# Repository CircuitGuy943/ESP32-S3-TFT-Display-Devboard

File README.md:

# ESP32 TFT Display Devboard

The ESP TFT Devboard is a devboard based on the ESP32-S3-WROOM-1 module with an integrated 40-pin connector designed to fully operate a TFT Display (one with a 3x8 RGB parallel interface) from the USB C connector only for power. It also has a bunch of breakout headers so that the GPIO pins can be accessed and used for other things, like a normal devboard whenever the display isn't being used. It consists of two USB C ports, one using the ESP32's built in USB connection and another using a USB to UART bridge (There is also a diode on each to ensure that the 5V doesn't backfeed if both USBs are connected). It then also consists of a boost converter to 24V for the LED Backlight and a current sink regulator to ensure it doesn't consume more than the rated current of 70mA.

## Features:
- Everything found on a normal devboard
- 2x USB C ports
- 24V, 5V and 3.3V outputs
- Support for a TFT 3x8 RGB display

## PCB
And this is my PCB. Very difficult to include everything in two layers but I managed to do it to save cost, and ommitted the use of an via in pads, the USB traces are length matched but the signals for the display don't need any trace/impedance matching as they don't run fast enough.

And the Schematic:

And here are some 3D views as well:

## Firmware Overview
I've included some basic firmware (**untested**) to get the TFT working but other than that it should function like a normal devboard hosting an ESP32

## BOM:
I have also included a .csv with the BOM list but here it is anyways.

 - 1x	CH340C	
 - 3x	Diode	
 - 2x	2N3904	
 - 2x	USB_C_Receptacle_USB2.0_16P	
 - 2x	5.7K	
 - 4x	5.1K	
 - 1x	47K	
 - 4x	1K	
 - 1x	1uF	
 - 3x	0.1uF
 - 4x	10uF
 - 6x	10K
 - 4x	27R
 - 1x	396K
 - 2x	100R
 - 1x	10K
 - 1x	MT3608
 - 1x	LD1117S33TR_SOT223
 - 1x	22R
 - 1x	ESP32-S3-WROOM-1
 - 2x	22uF
 - 1x	22uH
 - 2x	RED Led
 - 1x	GREEN Led
 - 2x	SW_Push
 - 1x	Conn_01x40_Socket
 - 1x	CAT4104
 - 1x	1.8K
 - 2x	Conn_01x14_Pin
 - 2x	Conn_01x04_Pin
 - 2x	Conn_01x09_Pin
(All parts for one devboard only)

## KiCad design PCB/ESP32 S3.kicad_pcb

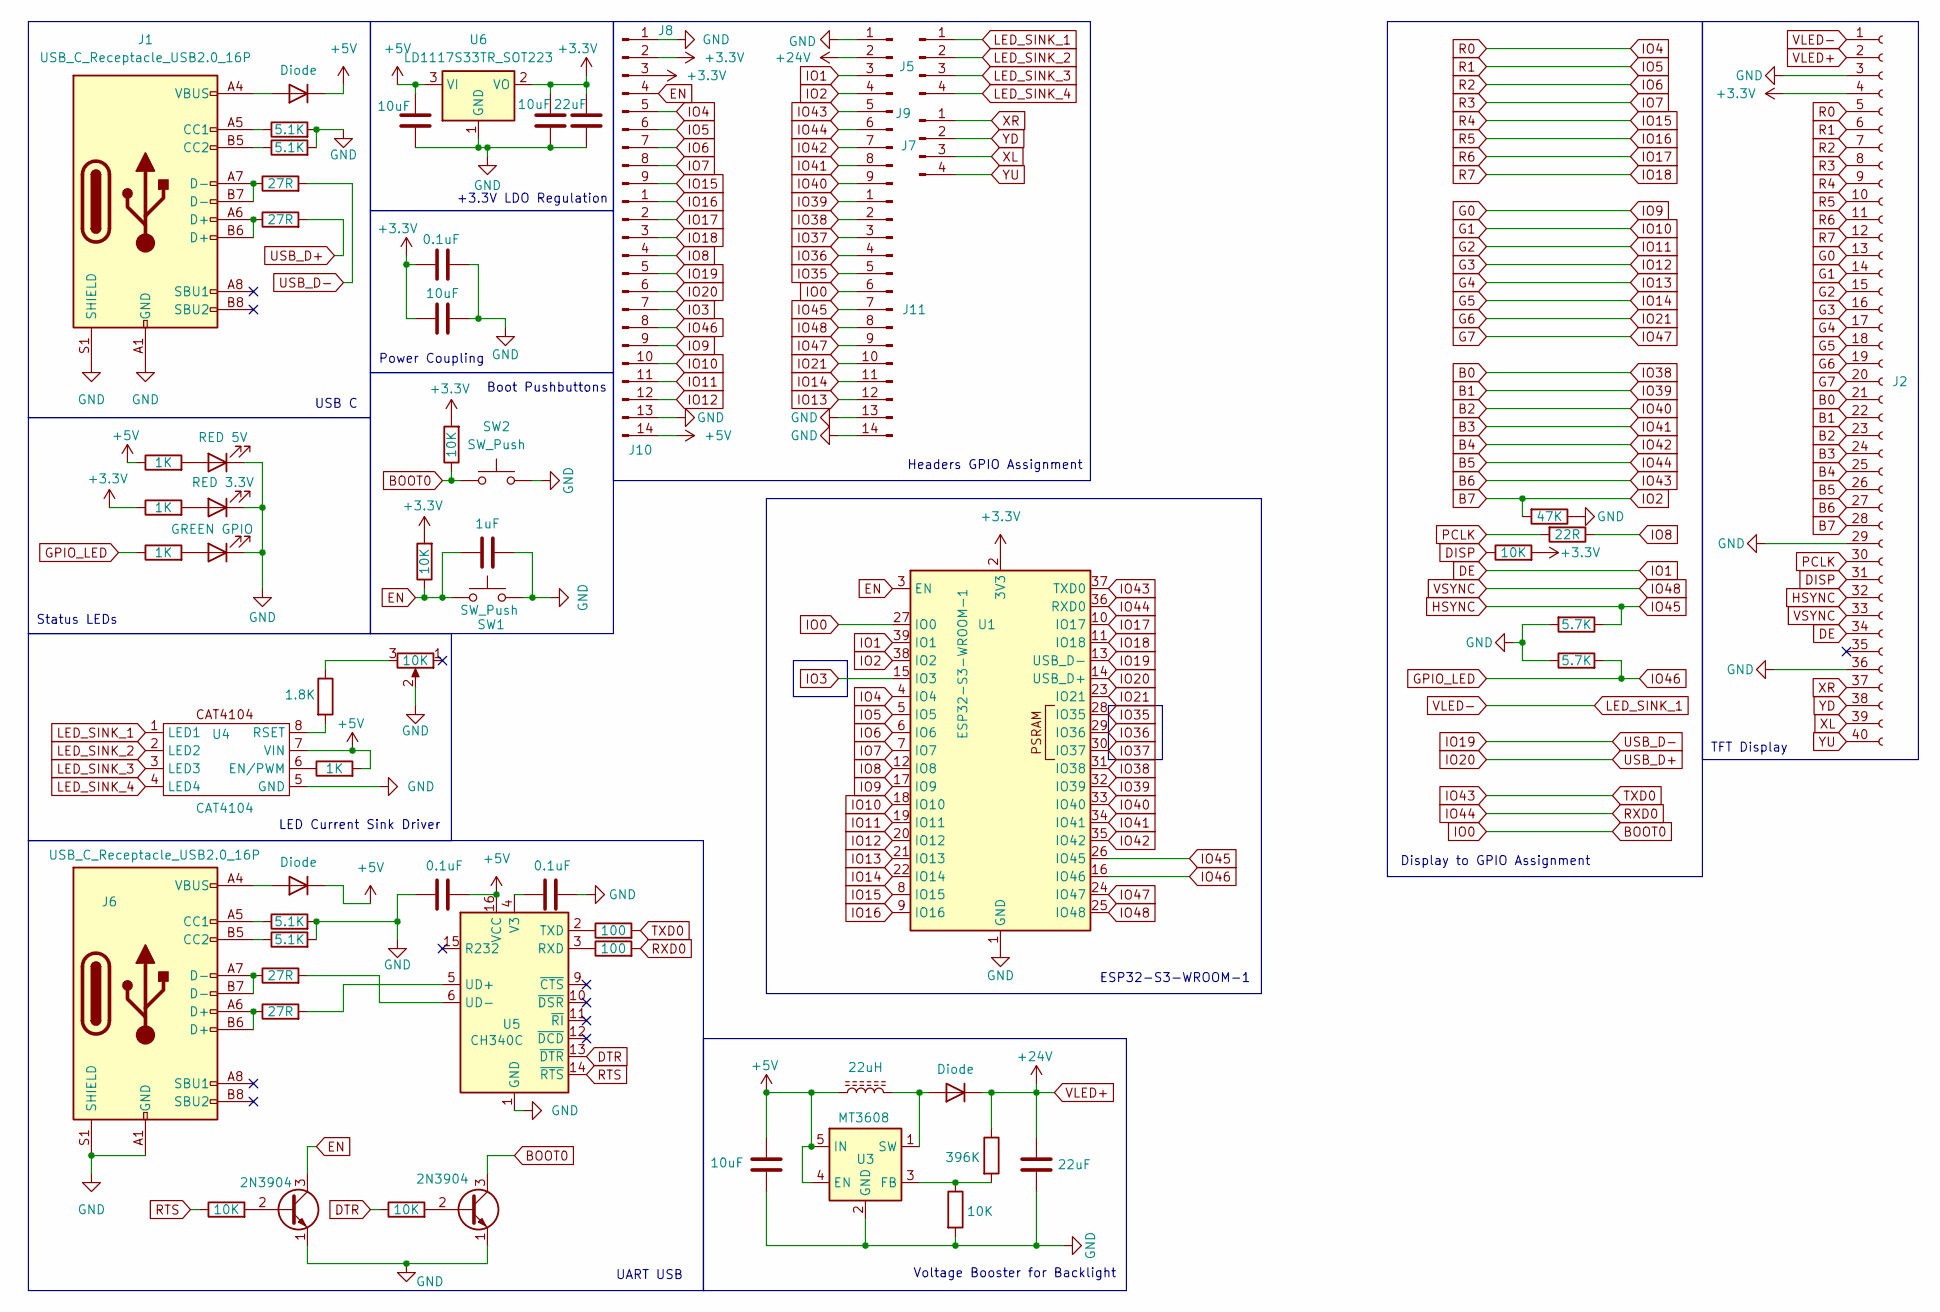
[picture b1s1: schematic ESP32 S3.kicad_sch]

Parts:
C1, C7, C8: 0.1uF; C_0402_1005Metric
C2, C3, C4, C6: 10uF; C_0603_1608Metric
C5, C9: 22uF; C_0603_1608Metric
C10: 1uF; C_0402_1005Metric
D1: RED 5V; LED_0402_1005Metric
D2: RED 3.3V; LED_0402_1005Metric
D3: GREEN GPIO; LED_0402_1005Metric
D4, D5, D6: Diode; D_SMB
J1, J6: USB_C_Receptacle_USB2.0_16P; USB_C_Receptacle_HCTL_HC-TYPE-C-16P-01A
J2: Conn_01x40_Socket; Hirose_FH12-40S-0.5SH_1x40-1MP_P0.50mm_Horizontal
J5, J7: Conn_01x04_Pin; PinHeader_1x04_P2.54mm_Vertical
J8, J9: Conn_01x09_Pin; PinHeader_1x09_P2.54mm_Vertical
J10, J11: Conn_01x14_Pin; PinHeader_1x14_P2.54mm_Vertical
L1: 22uH; 5028_SMD_INDUCTOR_SRR5028-220Y
Q1, Q2: 2N3904; SOT-23
R1, R2, R21, R22: 5.1K; R_0402_1005Metric
R3, R4, R19, R20: 27R; R_0402_1005Metric
R5, R6, R12, R14: 1K; R_0402_1005Metric
R7, R17: 5.7K; R_0402_1005Metric
R8, R9, R11, R15, R25, R26: 10K; R_0402_1005Metric
R10: 396K; R_0402_1005Metric
R13: 1.8K; R_0402_1005Metric
R18: 22R; R_0402_1005Metric
R23, R24: 100; R_0402_1005Metric
R27: 47K; R_0402_1005Metric
RV1: 10K; Potentiometer_Bourns_3314J_Vertical
SW1, SW2: SW_Push; SW_Push_1P1T-SH_NO_CK_KMR2xxG
U1: ESP32-S3-WROOM-1
U3: MT3608; SOT-23-6
U4: CAT4104
U5: CH340C; SOIC-16_3.9x9.9mm_P1.27mm
U6: LD1117S33TR_SOT223; SOT-223-3_TabPin2

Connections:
+3.3V: C1.2, C2.2, C4.2, C9.2, J2.4, J8.2, J8.3, R6.1, R8.2, R9.2, R15.2, U1.2 (3V3), U6.2 (VO)
+5V: C3.1, C6.2, C8.2, D5.1 (K), D6.1 (K), J10.14, L1.1, R5.1, R12.2, U3.4 (EN), U3.5 (IN), U4.7 (VIN), U5.16 (VCC), U6.3 (VI)
B0: J2.21, J11.2, U1.31 (IO38)
B1: J2.22, J11.1, U1.32 (IO39)
B2: J2.23, J9.9, U1.33 (IO40)
B3: J2.24, J9.8, U1.34 (IO41)
B4: J2.25, J9.7, U1.35 (IO42)
B5: J2.26, J9.6, R23.2, U1.36 (RXD0)
B6: J2.27, J9.5, R24.2, U1.37 (TXD0)
B7: J2.28, J9.4, R27.2, U1.38 (IO2)
BOOT0: J11.6, Q2.3 (C), R9.1, SW2.1, U1.27 (IO0)
DE: J2.34, J9.3, U1.39 (IO1)
DISP: J2.31, R15.1
DTR: R25.1, U5.13 (~DTR)
EN: C10.2, J8.4, Q1.3 (C), R8.1, SW1.1, U1.3 (EN)
G0: J2.13, J10.9, U1.17 (IO9)
G1: J2.14, J10.10, U1.18 (IO10)
G2: J2.15, J10.11, U1.19 (IO11)
G3: J2.16, J10.12, U1.20 (IO12)
G4: J2.17, J11.12, U1.21 (IO13)
G5: J2.18, J11.11, U1.22 (IO14)
G6: J2.19, J11.10, U1.23 (IO21)
G7: J2.20, J11.9, U1.24 (IO47)
GND: C1.1, C2.1, C3.2, C4.1, C5.1, C6.1, C7.2, C8.1, C9.1, C10.1, D1.1 (K), D2.1 (K), D3.1 (K), J1.A1 (GND), J1.A12 (GND), J1.B1 (GND), J1.B12 (GND), J1.S1 (SHIELD), J2.3, J2.29, J2.36, J2.MP, J6.A1 (GND), J6.A12 (GND), J6.B1 (GND), J6.B12 (GND), J6.S1 (SHIELD), J8.1, J9.1, J10.13, J11.13, J11.14, Q1.1 (E), Q2.1 (E), R1.2, R2.2, R7.1, R11.2, R17.2, R21.2, R22.2, R27.1, RV1.2, SW1.2, SW1.SH, SW2.2, SW2.SH, U1.1 (GND), U1.40 (GND), U1.41 (GND), U3.2 (GND), U4.5 (GND), U5.1 (GND), U6.1 (GND)
GPIO19: J10.5, R3.2, U1.13 (USB_D-)
GPIO20: J10.6, R4.2, U1.14 (USB_D+)
GPIO_LED: J10.8, R7.2, R14.1, U1.16 (IO46)
HSYNC: J2.32, J11.7, R17.1, U1.26 (IO45)
IO3: J10.7, U1.15 (IO3)
IO4: J2.5, J8.5, U1.4 (IO4)
IO5: J2.6, J8.6, U1.5 (IO5)
IO6: J2.7, J8.7, U1.6 (IO6)
IO7: J2.8, J8.8, U1.7 (IO7)
IO8: J10.4, R18.1, U1.12 (IO8)
IO15: J2.9, J8.9, U1.8 (IO15)
IO16: J2.10, J10.1, U1.9 (IO16)
IO17: J2.11, J10.2, U1.10 (IO17)
IO18: J2.12, J10.3, U1.11 (IO18)
IO35: J11.5, U1.28 (IO35)
IO36: J11.4, U1.29 (IO36)
IO37: J11.3, U1.30 (IO37)
IO48: J2.33, J11.8, U1.25 (IO48)
LED_SINK_1: J2.1, J5.1, U4.1 (LED1)
LED_SINK_2: J5.2, U4.2 (LED2)
LED_SINK_3: J5.3, U4.3 (LED3)
LED_SINK_4: J5.4, U4.4 (LED4)
unnamed: D1.2 (A), R5.2
unnamed: D2.2 (A), R6.2
unnamed: D3.2 (A), R14.2
unnamed: D4.2 (A), L1.2, U3.1 (SW)
unnamed: D5.2 (A), J6.A4 (VBUS), J6.A9 (VBUS), J6.B4 (VBUS), J6.B9 (VBUS)
unnamed: D6.2 (A), J1.A4 (VBUS), J1.A9 (VBUS), J1.B4 (VBUS), J1.B9 (VBUS)
unnamed: J1.A5 (CC1), R1.1
unnamed: J1.B5 (CC2), R2.1
unnamed: J1.A6 (D+), J1.B6 (D+), R4.1
unnamed: J1.A7 (D-), J1.B7 (D-), R3.1
unnamed: J6.A5 (CC1), R21.1
unnamed: J6.B5 (CC2), R22.1
unnamed: J6.A6 (D+), J6.B6 (D+), R20.1
unnamed: J6.A7 (D-), J6.B7 (D-), R19.1
unnamed: Q1.2 (B), R26.2
unnamed: Q2.2 (B), R25.2
unnamed: R13.1, RV1.3
unnamed: R10.2, R11.1, U3.3 (FB)
unnamed: R12.1, U4.6 (EN/PWM)
unnamed: R13.2, U4.8 (RSET)
unnamed: R23.1, U5.3 (RXD)
unnamed: R24.1, U5.2 (TXD)
unnamed: R20.2, U5.5 (UD+)
unnamed: R19.2, U5.6 (UD-)
unnamed: C7.1, U5.4 (V3)
PCLK: J2.30, R18.2
RTS: R26.1, U5.14 (~RTS)
VLED+: C5.2, D4.1 (K), J2.2, J9.2, R10.1
XL: J2.39, J7.3
XR: J2.37, J7.1
YD: J2.38, J7.2
YU: J2.40, J7.4

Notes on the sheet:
UART USB
USB C
Boot Pushbuttons
+3.3V LDO Regulation
Power Coupling
Status LEDs
LED Current Sink Driver
ESP32-S3-WROOM-1
TFT Display
Headers GPIO Assignment
Display to GPIO Assignment
Voltage Booster for Backlight

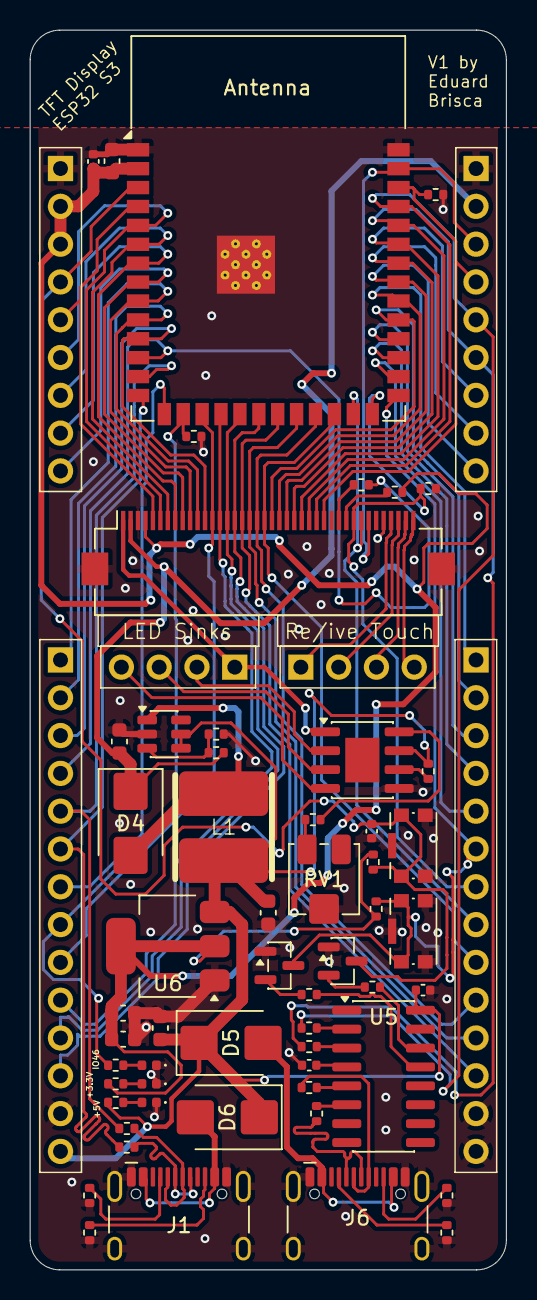
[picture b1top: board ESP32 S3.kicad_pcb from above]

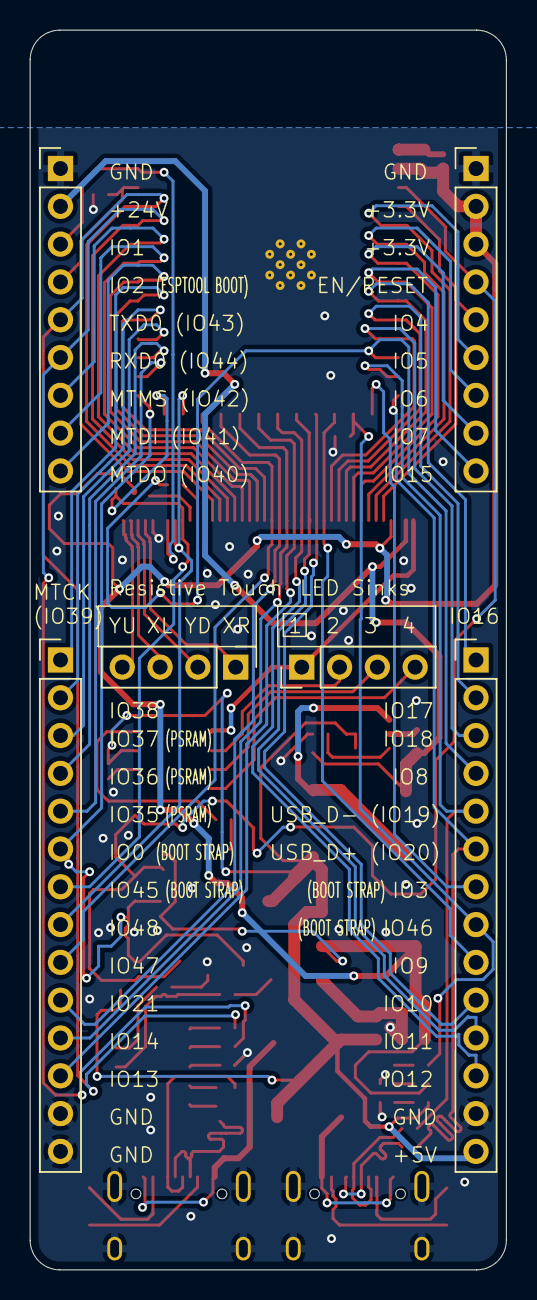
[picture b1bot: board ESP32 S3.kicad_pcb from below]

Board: 2 copper layers, 32.0 x 83.3 mm, 62 parts (6 on the bottom side), 78 nets.

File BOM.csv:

Quantity,Comment,
1,CH340C,
3,Diode,
2,2N3904,
2,USB_C_Receptacle_USB2.0_16P,
2,5.7K,
4,5.1K,
1,47K,
4,1K,
1,1uF,
3,0.1uF,
4,10uF,
6,10K,
4,27R,
1,396K,
2,100R,
1,10K,
1,MT3608,
1,LD1117S33TR_SOT223,
1,22R,
1,ESP32-S3-WROOM-1,
2,22uF,
1,22uH,
1,RED 3.3V,
1,RED 5V,
1,GREEN GPIO,
2,SW_Push,
1,Conn_01x40_Socket,
1,CAT4104,
1,1.8K,
2,Conn_01x14_Pin,
2,Conn_01x04_Pin,
2,Conn_01x09_Pin,(All parts for one devboard only)
,,
Total Component Price:,£17.85,
PCB Price:,£2.37,
Rest of PCBA,£59.41,
,,
Total,£79.63,

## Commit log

2025-12-30 Update with a few improvments
2026-01-02 Create LICENSE
2026-03-08 Add pictures and problem txt
